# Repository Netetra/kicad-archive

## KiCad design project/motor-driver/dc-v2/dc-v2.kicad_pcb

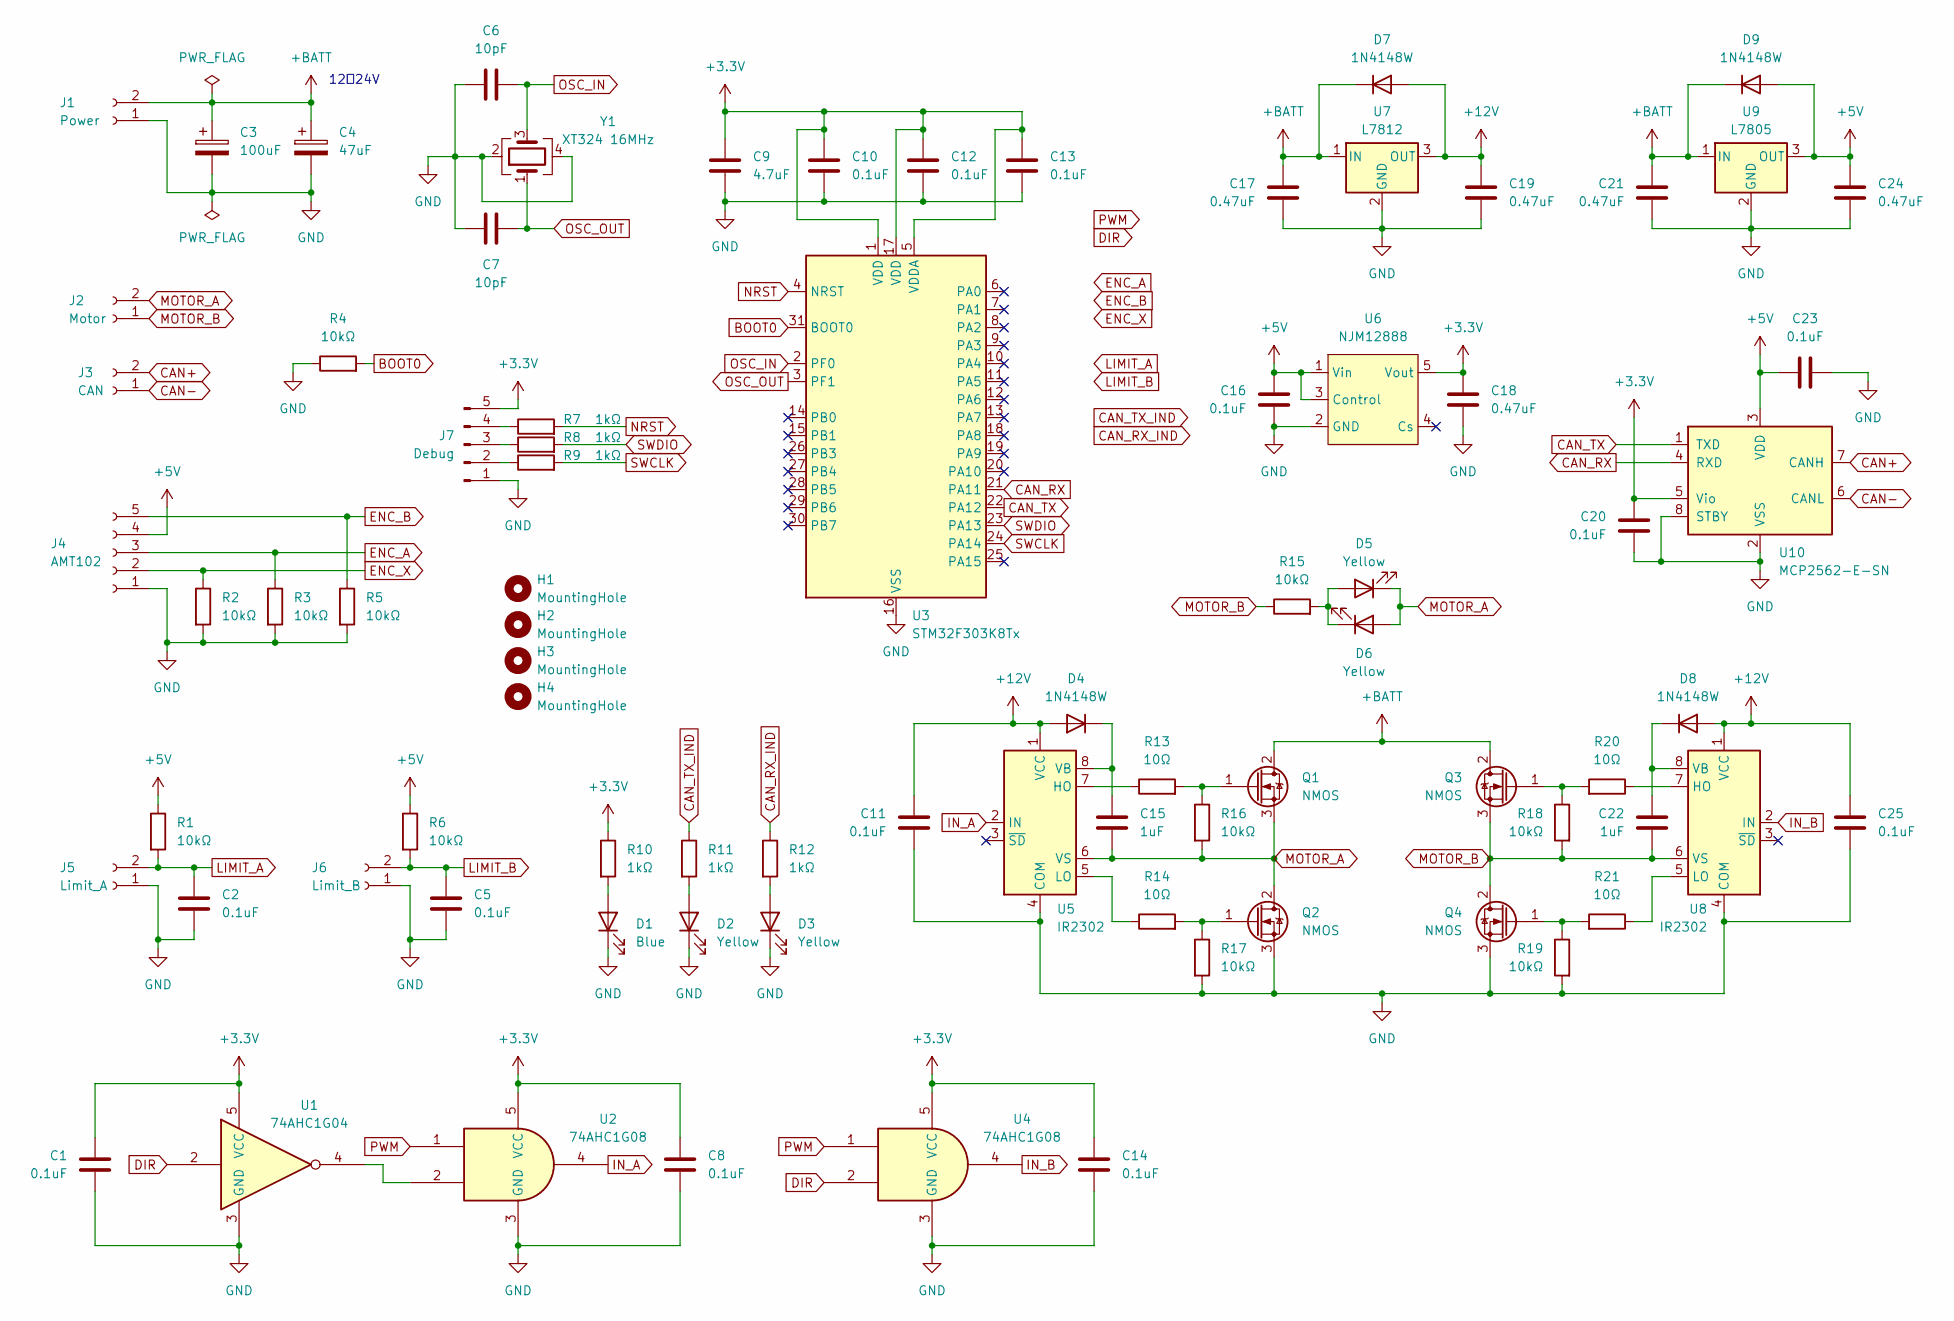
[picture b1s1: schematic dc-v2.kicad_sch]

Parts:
C1, C2, C5, C8, C10, C11, C12, C13, C14, C16, C20, C23, C25: 0.1uF; C_0603_1608Metric
C3: 100uF; CP_Radial_D8.0mm_P3.50mm
C4: 47uF; CP_Radial_D6.3mm_P2.50mm
C6, C7: 10pF; C_0603_1608Metric
C9: 4.7uF; C_0603_1608Metric
C15, C22: 1uF; C_0805_2012Metric
C17, C18, C19, C21, C24: 0.47uF; C_0603_1608Metric
D1: Blue; LED_0603_1608Metric
D2, D3, D5, D6: Yellow; LED_0603_1608Metric
D4, D7, D8, D9: 1N4148W; D_SOD-123
H1, H2, H3, H4: MountingHole; MountingHole_3.2mm_M3
J1: Power; AMASS_XT30PW-M_1x02_P2.50mm_Horizontal
J2: Motor; AMASS_XT30PW-F_1x02_P2.50mm_Horizontal
J3: CAN; JST_XA_S02B-XASK-1N-BN_1x02_P2.50mm_Horizontal
J4: AMT102; JST_XH_S5B-XH-A_1x05_P2.50mm_Horizontal
J5: Limit_A; JST_XH_S2B-XH-A_1x02_P2.50mm_Horizontal
J6: Limit_B; JST_XH_S2B-XH-A_1x02_P2.50mm_Horizontal
J7: Debug; PinSocket_1x05_P2.54mm_Horizontal
Q1, Q2, Q3, Q4: NMOS; TO-252-2
R1, R2, R3, R4, R5, R6, R15, R16, R17, R18, R19: 10kΩ; R_0603_1608Metric
R7, R8, R9, R10, R11, R12: 1kΩ; R_0603_1608Metric
R13, R14, R20, R21: 10Ω; R_0603_1608Metric
U1: 74AHC1G04; SOT-23-5
U2, U4: 74AHC1G08; SOT-23-5
U3: STM32F303K8Tx; LQFP-32_7x7mm_P0.8mm
U5, U8: IR2302; SOIC-8_3.9x4.9mm_P1.27mm
U6: NJM12888; SOT-23-5
U7: L7812; TO-252-2
U9: L7805; TO-252-2
U10: MCP2562-E-SN; SOIC-8_3.9x4.9mm_P1.27mm
Y1: XT324 16MHz; Crystal_SMD_3225-4Pin_3.2x2.5mm

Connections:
+3.3V: C1.1, C8.1, C9.1, C10.1, C12.1, C13.1, C14.1, C18.1, C20.2, J7.5, R10.1, U1.5 (VCC), U2.5 (VCC), U3.1 (VDD), U3.5 (VDDA), U3.17 (VDD), U4.5 (VCC), U6.5 (Vout), U10.5 (Vio)
+5V: C16.1, C23.2, C24.1, D9.2 (A), J4.4, R1.1, R6.1, U6.1 (Vin), U6.3 (Control), U9.3 (OUT), U10.3 (VDD)
+12V: C11.1, C19.1, C25.1, D4.2 (A), D7.2 (A), D8.2 (A), U5.1 (VCC), U7.3 (OUT), U8.1 (VCC)
+BATT: C3.1, C4.1, C17.1, C21.1, D7.1 (K), D9.1 (K), J1.2, Q1.2 (D), Q3.2 (D), U7.1 (IN), U9.1 (IN)
BOOT0: R4.2, U3.31 (BOOT0)
CAN+: J3.2, U10.7 (CANH)
CAN-: J3.1, U10.6 (CANL)
CAN_RX: U3.21 (PA11), U10.4 (RXD)
CAN_RX_IND: R12.1
CAN_TX: U3.22 (PA12), U10.1 (TXD)
CAN_TX_IND: R11.1
DIR: U1.2, U4.2
ENC_A: J4.3, R3.1
ENC_B: J4.5, R5.1
ENC_X: J4.2, R2.1
GND: C1.2, C2.2, C3.2, C4.2, C5.2, C6.1, C7.1, C8.2, C9.2, C10.2, C11.2, C12.2, C13.2, C14.2, C16.2, C17.2, C18.2, C19.2, C20.1, C21.2, C23.1, C24.2, C25.2, D1.1 (K), D2.1 (K), D3.1 (K), J1.1, J4.1, J5.1, J6.1, J7.1, Q2.3 (S), Q4.3 (S), R2.2, R3.2, R4.1, R5.2, R17.2, R19.2, U1.3 (GND), U2.3 (GND), U3.16 (VSS), U3.32 (VSS), U4.3 (GND), U5.4 (COM), U6.2 (GND), U7.2 (GND), U8.4 (COM), U9.2 (GND), U10.2 (VSS), U10.8 (STBY), Y1.2, Y1.4
IN_A: U2.4, U5.2 (IN)
IN_B: U4.4, U8.2 (IN)
LIMIT_A: C2.1, J5.2, R1.2
LIMIT_B: C5.1, J6.2, R6.2
MOTOR_A: C15.2, D5.1 (K), D6.2 (A), J2.2, Q1.3 (S), Q2.2 (D), R16.2, U5.6 (VS)
MOTOR_B: C22.2, J2.1, Q3.3 (S), Q4.2 (D), R15.1, R18.2, U8.6 (VS)
NRST: R7.2, U3.4 (NRST)
unnamed: D1.2 (A), R10.2
unnamed: D2.2 (A), R11.2
unnamed: D3.2 (A), R12.2
unnamed: C15.1, D4.1 (K), U5.8 (VB)
unnamed: D5.2 (A), D6.1 (K), R15.2
unnamed: C22.1, D8.1 (K), U8.8 (VB)
unnamed: J7.2, R9.1
unnamed: J7.3, R8.1
unnamed: J7.4, R7.1
unnamed: Q1.1 (G), R13.2, R16.1
unnamed: Q2.1 (G), R14.2, R17.1
unnamed: Q3.1 (G), R18.1, R20.2
unnamed: Q4.1 (G), R19.1, R21.2
unnamed: U1.4, U2.2
unnamed: R13.1, U5.7 (HO)
unnamed: R14.1, U5.5 (LO)
unnamed: R20.1, U8.7 (HO)
unnamed: R21.1, U8.5 (LO)
OSC_IN: C6.2, U3.2 (PF0), Y1.3
OSC_OUT: C7.2, U3.3 (PF1), Y1.1
PWM: U2.1, U4.1
SWCLK: R9.2, U3.24 (PA14)
SWDIO: R8.2, U3.23 (PA13)

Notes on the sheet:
12〜24V

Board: 2 copper layers, 81 parts (0 on the bottom side), 44 nets, no tracks yet.

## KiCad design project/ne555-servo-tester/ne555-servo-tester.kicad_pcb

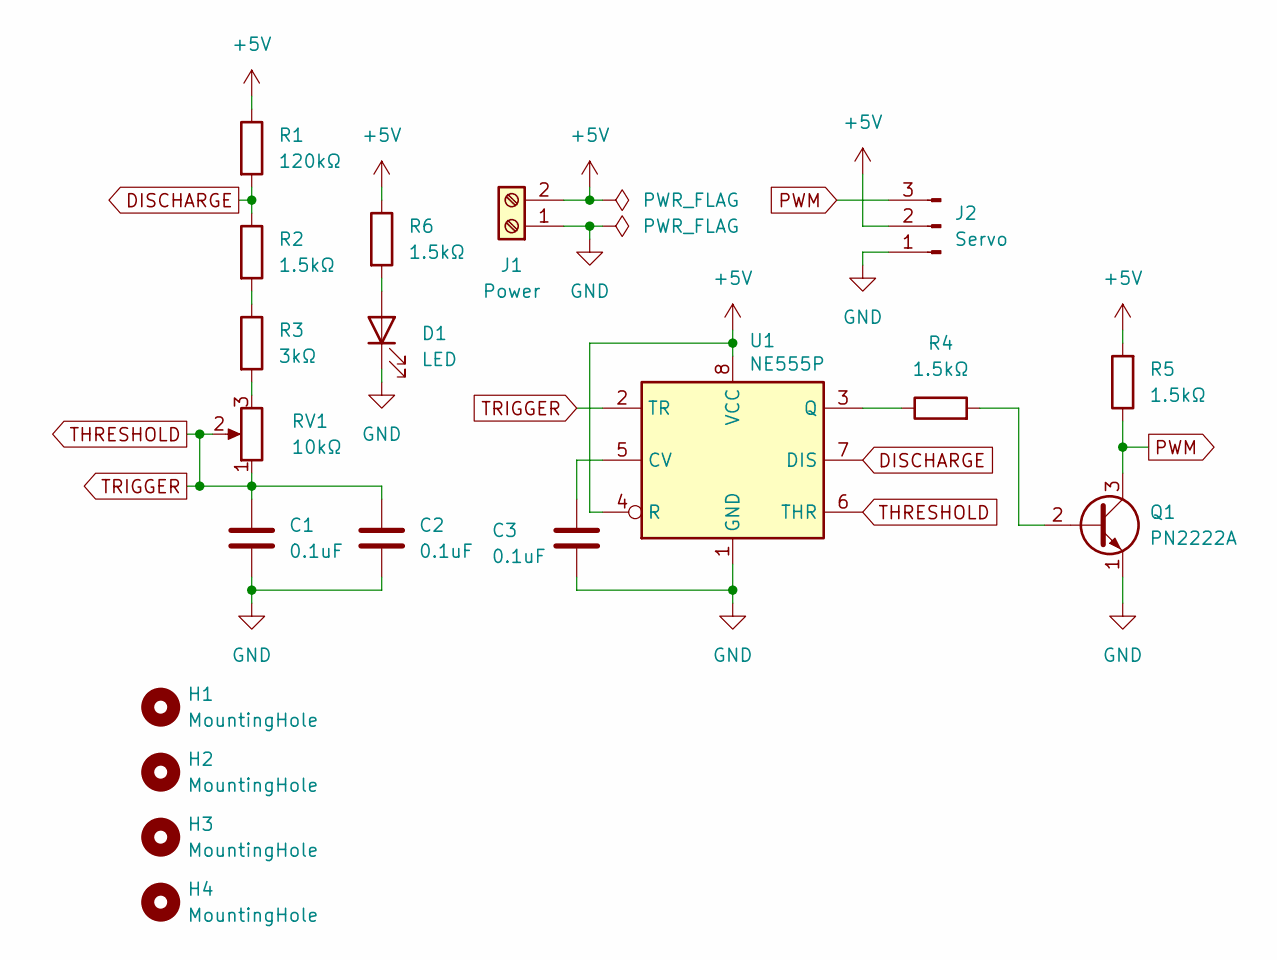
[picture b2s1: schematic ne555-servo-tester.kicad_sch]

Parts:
C1, C2, C3: 0.1uF; C_Disc_D3.0mm_W2.0mm_P2.50mm
D1: LED; LED_D5.0mm
H1, H2, H3, H4: MountingHole; MountingHole_3.2mm_M3
J1: Power; TerminalBlock_MetzConnect_Type101_RT01602HBWC_1x02_P5.08mm_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
J2: Servo; PinHeader_1x03_P2.54mm_Vertical
Q1: PN2222A; TO-92_Inline
R1: 120kΩ; R_Axial_DIN0207_L6.3mm_D2.5mm_P10.16mm_Horizontal
R2, R4, R5, R6: 1.5kΩ; R_Axial_DIN0207_L6.3mm_D2.5mm_P10.16mm_Horizontal
R3: 3kΩ; R_Axial_DIN0207_L6.3mm_D2.5mm_P10.16mm_Horizontal
RV1: 10kΩ; Potentiometer_Piher_PT-6-V_Vertical
U1: NE555P; DIP-8_W7.62mm

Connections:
+5V: J1.2, J2.2, R1.1, R5.2, R6.1, U1.4 (R), U1.8 (VCC)
DISCHARGE: R1.2, R2.1, U1.7 (DIS)
GND: C1.2, C2.2, C3.2, D1.1 (K), J1.1, J2.1, Q1.1 (E), U1.1 (GND)
unnamed: D1.2 (A), R6.2
unnamed: Q1.2 (B), R4.2
unnamed: R2.2, R3.1
unnamed: R3.2, RV1.3
unnamed: C3.1, U1.5 (CV)
unnamed: R4.1, U1.3 (Q)
PWM: J2.3, Q1.3 (C), R5.1
THRESHOLD: C1.1, C2.1, RV1.1, RV1.2, U1.2 (TR), U1.6 (THR)

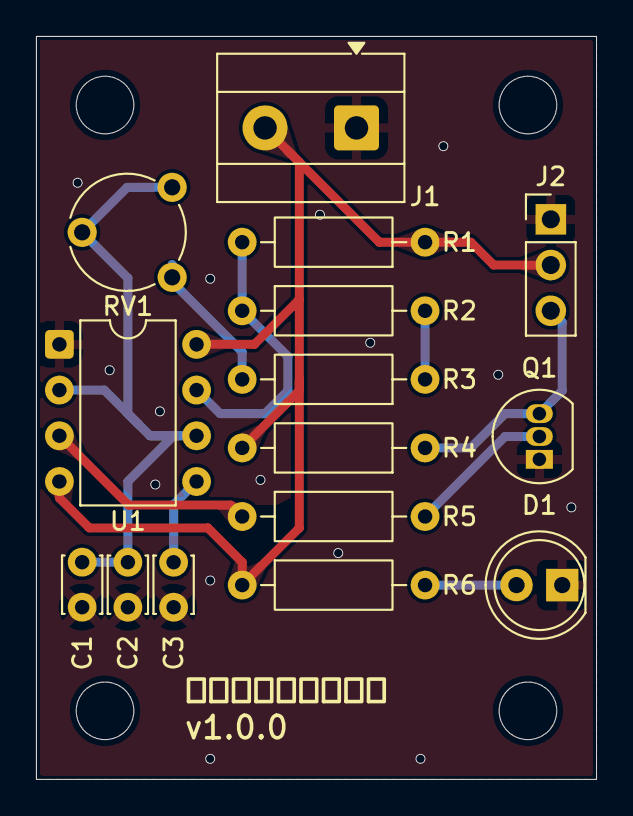
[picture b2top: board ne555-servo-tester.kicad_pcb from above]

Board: 2 copper layers, 31.1 x 41.3 mm, 19 parts (0 on the bottom side), 11 nets.

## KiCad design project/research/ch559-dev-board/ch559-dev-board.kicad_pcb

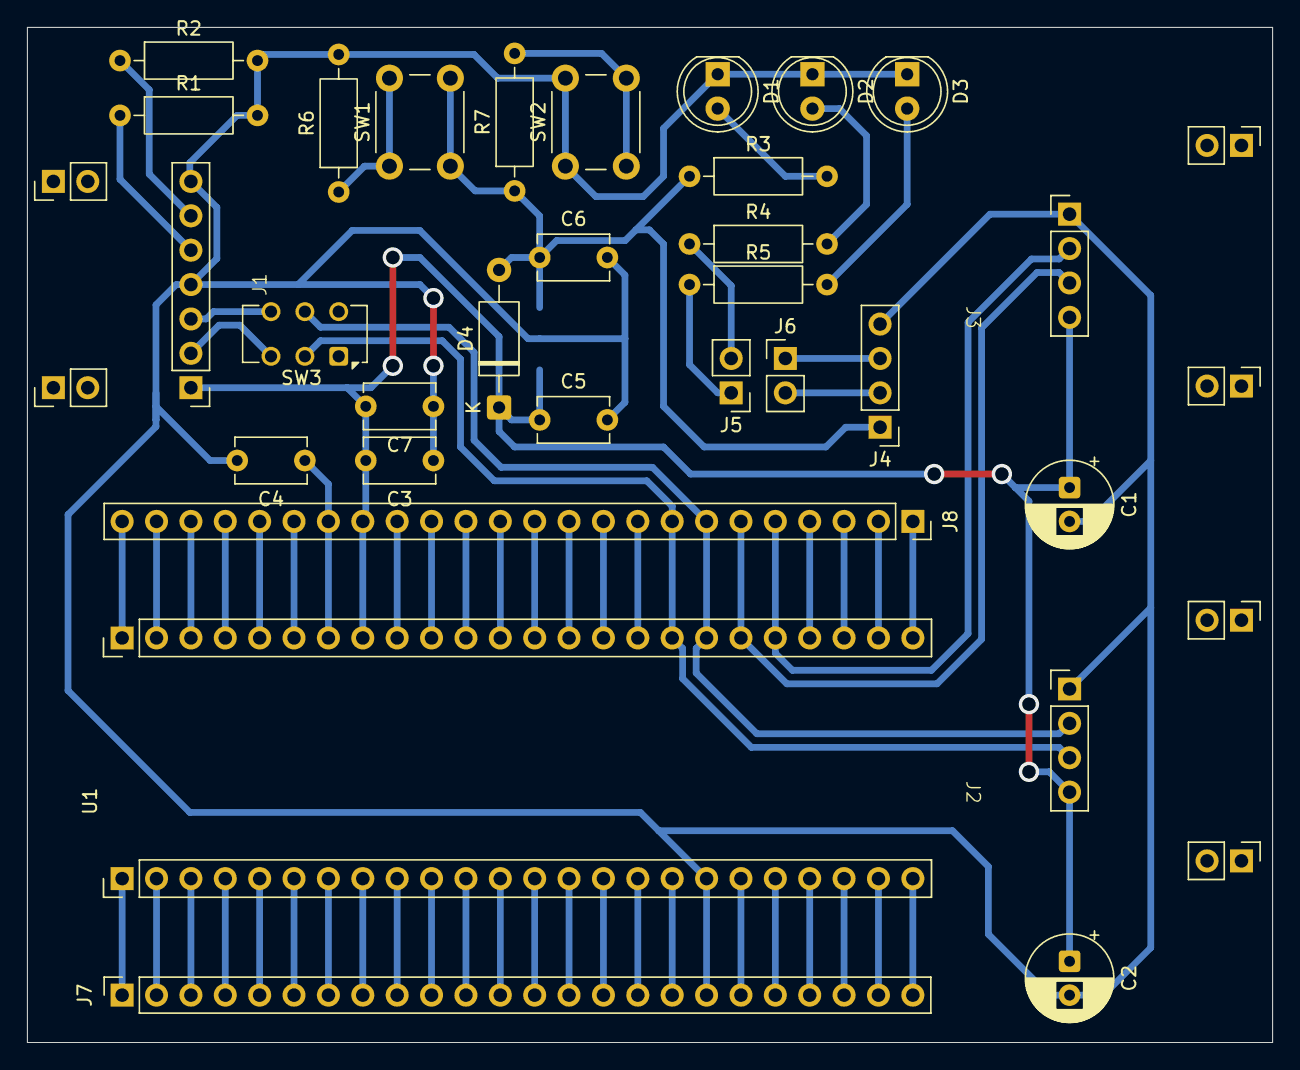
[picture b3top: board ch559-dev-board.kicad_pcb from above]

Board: 2 copper layers, 92.0 x 75.0 mm, 31 parts (1 on the bottom side), 60 nets.

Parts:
C1, C2: 22uF; CP_Radial_D6.3mm_P2.50mm
C3: 0.1uF; C_Disc_D5.1mm_W3.2mm_P5.00mm
C4: 4.7uF; C_Disc_D5.1mm_W3.2mm_P5.00mm
C5: 10uF; C_Disc_D5.1mm_W3.2mm_P5.00mm
C6: 22uF; C_Disc_D5.1mm_W3.2mm_P5.00mm
C7: 1uF; C_Disc_D5.1mm_W3.2mm_P5.00mm
D1, D2, D3: LED; LED_D5.0mm
D4: D_Schottky; D_A-405_P10.16mm_Horizontal
J1: USB_C_Receptacle_USB2.0_16P; usbc-dip
J2, J3: USB_A; usb-dip
J4: UART; PinHeader_1x04_P2.54mm_Vertical
J5: LED; PinHeader_1x02_P2.54mm_Vertical
J6: UART_SIG; PinHeader_1x02_P2.54mm_Vertical
J7, J8: Conn_01x24_Pin; PinSocket_1x24_P2.54mm_Vertical
R1, R2: 5.1kΩ; R_Axial_DIN0207_L6.3mm_D2.5mm_P10.16mm_Horizontal
R3, R4, R5, R6, R7: 1kΩ; R_Axial_DIN0207_L6.3mm_D2.5mm_P10.16mm_Horizontal
SW1: RESET; SW_PUSH_6mm
SW2: BOOT; SW_PUSH_6mm
SW3: SW_Slide_DPDT; SW_CK_JS202011CQN_DPDT_Straight
U1: CH559L; qfp48-dip
U2: AZ1117CH2-3.3; SOT-223-3_TabPin2

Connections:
1: J7.1, U1.1 (P1.6)
2: J7.2, U1.2 (P1.7)
4: J7.4, U1.4 (P3.0)
5: J7.5, U1.5 (P4.5)
6: J7.6, U1.6 (P4.4)
7: J7.7, U1.7 (P3.1)
8: J7.8, U1.8 (P3.2)
9: J7.9, U1.9 (P3.3)
10: J7.10, U1.10 (P3.4)
11: J7.11, U1.11 (P3.5)
12: J7.12, U1.12 (P3.6)
13: J7.13, U1.13 (P3.7)
14: J7.14, U1.14 (P4.3)
15: J7.15, U1.15 (P4.2)
17: J7.17, U1.17 (P4.7)
19: J7.19, U1.19 (P4.1)
20: J7.20, U1.20 (P4.0)
21: J7.21, U1.21 (P2.0)
22: J7.22, U1.22 (P2.1)
23: J7.23, U1.23 (P2.2)
24: J7.24, U1.24 (P2.3)
25: J8.1, U1.25 (P2.4)
26: J8.2, U1.26 (P2.5)
27: J8.3, U1.27 (P2.6)
28: J8.4, U1.28 (P2.7)
33: J8.9, U1.33 (P0.7)
34: J8.10, U1.34 (P0.6)
35: J8.11, U1.35 (P0.5)
36: J8.12, U1.36 (P0.4)
37: J8.13, U1.37 (P0.3)
38: J8.14, U1.38 (P0.2)
39: J8.15, U1.39 (P0.1)
40: J8.16, U1.40 (P0.0)
42: C4.1, J8.18, U1.42 (VDD33)
43: J8.19, U1.43 (P1.0)
44: J8.20, U1.44 (P1.1)
45: J8.21, U1.45 (P1.2)
46: J8.22, U1.46 (P1.3)
47: J8.23, U1.47 (P1.4)
48: J8.24, U1.48 (P1.5)
+3.3V: C6.1, D4.2 (A), J4.1, R3.1, R7.1, SW1.2, U2.3 (OUT)
BOOT: J7.16, R7.2, SW2.2, U1.16 (P4.6)
D0+: J2.3 (D+), J8.7, SW3.5 (B), U1.31 (DP0)
D0-: J2.2 (D-), J8.8, SW3.2 (B), U1.32 (DM0)
D1+: J3.3 (D+), J8.5, U1.29 (DP1)
D1-: J3.2 (D-), J8.6, U1.30 (DM1)
GND: C1.2, C2.2, C3.1, C4.2, C5.2, C6.2, C7.1, D1.1 (K), D2.1 (K), D3.1 (K), J1.A1 (GND), J1.S1 (SHIELD), J2.4 (GND), J3.4 (GND), J4.4, J7.18, R1.2, R2.2, R6.2, SW2.1, U1.18 (GND), U2.2 (GND)
unnamed: D1.2 (A), R3.2
unnamed: D2.2 (A), R4.2
unnamed: D3.2 (A), R5.2
unnamed: J1.A5 (CC1), R1.1
unnamed: J1.B5 (CC2), R2.1
unnamed: J4.2, J6.2
unnamed: J4.3, J6.1
unnamed: J5.1, R5.1
unnamed: J5.2, R4.1
RST: J7.3, R6.1, SW1.1, U1.3 (RST)
VBUS: C1.1, C2.1, C3.2, C5.1, C7.2, D4.1 (K), J1.A4 (VBUS), J2.1 (VBUS), J3.1 (VBUS), J8.17, U1.41 (VIN5), U2.1 (IN)
aD0+: J1.A6 (D+), SW3.4 (A)
aD0-: J1.A7 (D-), SW3.3 (C)

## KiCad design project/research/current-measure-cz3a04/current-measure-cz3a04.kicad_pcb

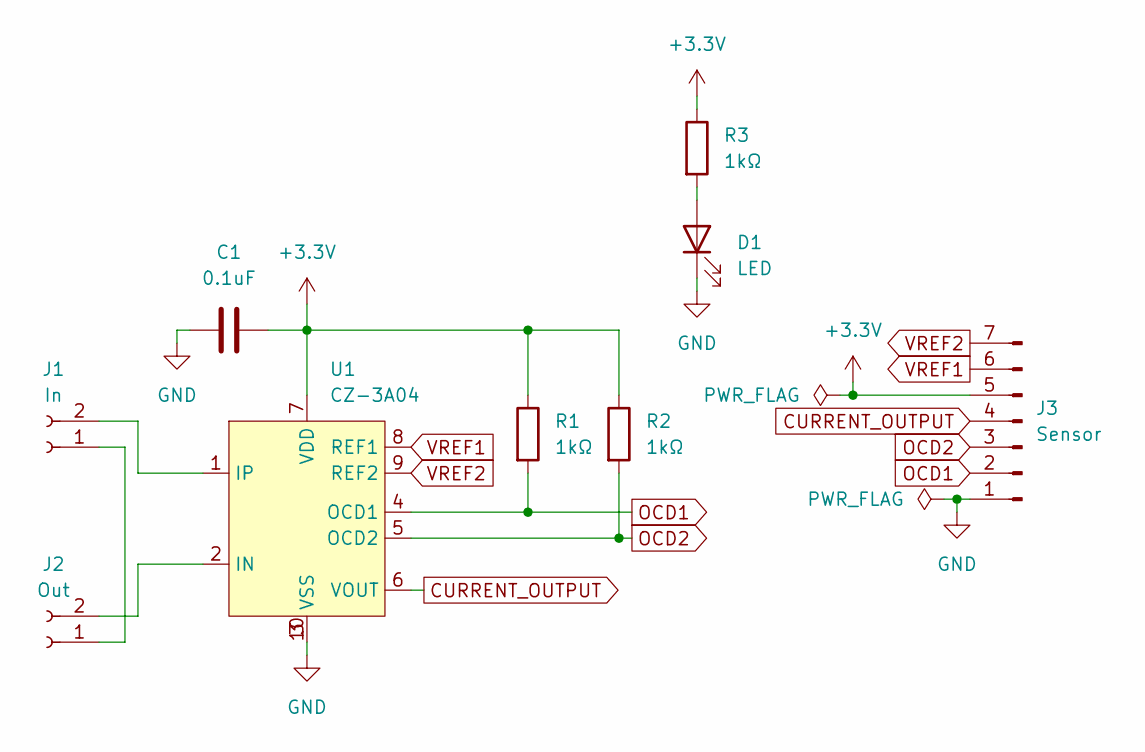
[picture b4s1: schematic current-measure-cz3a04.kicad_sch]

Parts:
C1: 0.1uF; C_Disc_D5.1mm_W3.2mm_P5.00mm
D1: LED; LED_D5.0mm
J1: In; AMASS_XT60-M_1x02_P7.20mm_Vertical
J2: Out; AMASS_XT60-F_1x02_P7.20mm_Vertical
J3: Sensor; PinHeader_1x07_P2.54mm_Vertical
R1, R2, R3: 1kΩ; R_Axial_DIN0207_L6.3mm_D2.5mm_P10.16mm_Horizontal
U1: CZ-3A04; AKM_CZ_SSOP-alt

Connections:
+3.3V: C1.1, J3.5, R1.1, R2.1, R3.1, U1.7 (VDD)
CURRENT_OUTPUT: J3.4, U1.6 (VOUT)
GND: C1.2, D1.1 (K), J3.1, U1.3 (VSS), U1.10 (VSS)
unnamed: D1.2 (A), R3.2
unnamed: J1.1, J2.1
unnamed: J1.2, U1.1 (IP)
unnamed: J2.2, U1.2 (IN)
OCD1: J3.2, R1.2, U1.4 (OCD1)
OCD2: J3.3, R2.2, U1.5 (OCD2)
VREF1: J3.6, U1.8 (REF1)
VREF2: J3.7, U1.9 (REF2)

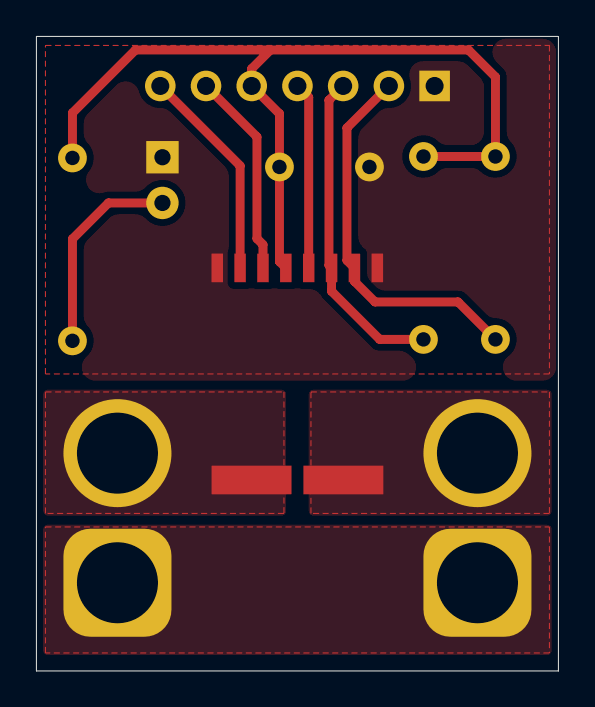
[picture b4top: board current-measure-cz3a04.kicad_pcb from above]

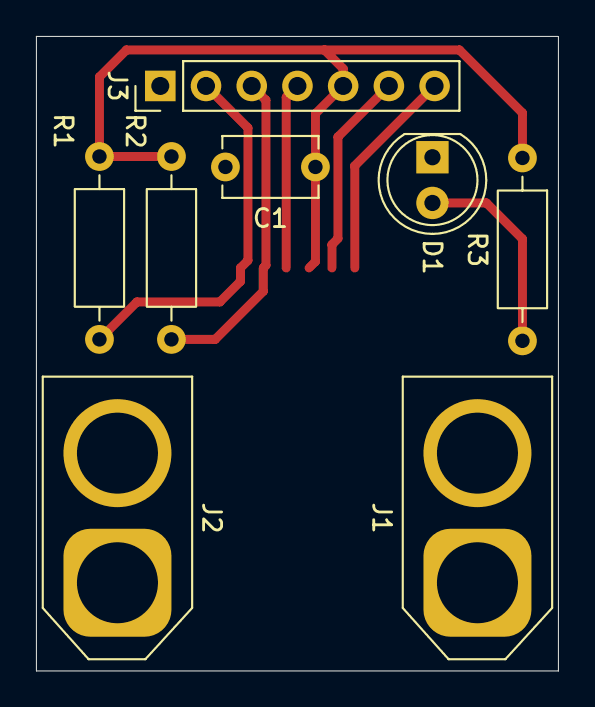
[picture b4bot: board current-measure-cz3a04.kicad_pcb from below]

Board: 2 copper layers, 29.0 x 35.2 mm, 9 parts (8 on the bottom side), 11 nets.

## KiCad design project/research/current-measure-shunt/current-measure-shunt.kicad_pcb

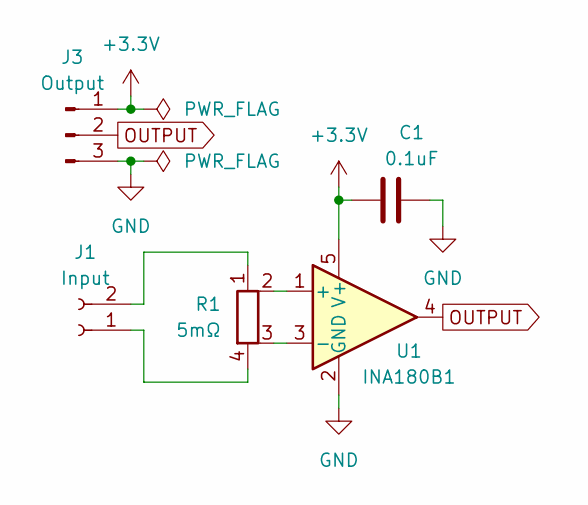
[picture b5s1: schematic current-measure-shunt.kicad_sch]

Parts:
C1: 0.1uF; C_0603_1608Metric
J1: Input; AMASS_XT30U-M_1x02_P5.0mm_Vertical
J3: Output; PinSocket_1x03_P2.54mm_Vertical
R1: 5mΩ; R_Shunt_Vishay_WSK2512_6332Metric_T1.19mm
U1: INA180B1; SOT-23-5

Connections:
+3.3V: C1.1, J3.1, U1.5 (V+)
GND: C1.2, J3.3, U1.2 (GND)
unnamed: J1.1, R1.4
unnamed: J1.2, R1.1
unnamed: R1.2, U1.1 (+)
unnamed: R1.3, U1.3 (-)
OUTPUT: J3.2, U1.4

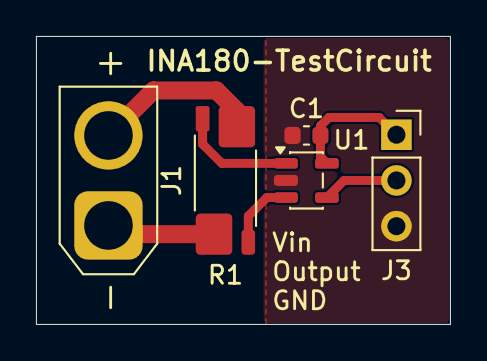
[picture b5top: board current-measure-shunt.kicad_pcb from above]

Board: 2 copper layers, 23.0 x 16.0 mm, 5 parts (0 on the bottom side), 7 nets.

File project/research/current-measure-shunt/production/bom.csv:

Designator,Footprint,Quantity,Value,LCSC Part #
C1,0603,1,0.1uF,
J1,AMASS_XT30U-M_1x02_P5.0mm_Vertical,1,Input,
J3,PinSocket_1x03_P2.54mm_Vertical,1,Output,
R1,R_Shunt_Vishay_WSK2512_6332Metric_T1.19mm,1,5mΩ,
U1,SOT-23-5,1,INA180B1,
